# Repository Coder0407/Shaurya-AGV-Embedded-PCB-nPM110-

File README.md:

# Shaurya-AGV-Embedded-PCB-nPM110-

This project involves the design and layout of a high-efficiency Power Management Module based on the Nordic nPM1100 PMIC. The board is engineered to provide a robust 3V logic rail at a nominal 200ma charging rate.
The PCB follows a 2-Layer approach where Copper Pour(Ground) has been done on both planes with a primary focus on maintaining a solid, contiguous Ground Plane on the bottom layer. By minimizing signal routing on the bottom a low-impedance return path for the high-frequency switching currents is ensured 
The Designs prioritises Power integrety , a effort has been made into ensuring minimum SW- trace and keeping the decoupling capacitors as close as possible with multiple ground vias attached to them
Various LED for power CHG and ERR are placed , MCU is exposed to multiple pins including CHG ERR Mode SHPACT and a battery charge monitering system has been introduced.
A switch has also been connected to SHPLD to turn on the IC manually.
Values of various Pins like VSET and resistance like R_ICHG are tune to ensure a 200ma nominal charging current and a max 4.2VBAT with the data from the datasheet.
In the battery monitering system the MCU is given controll through Q1 and Q2 on when to measure the battery voltage, to reduce power loss .

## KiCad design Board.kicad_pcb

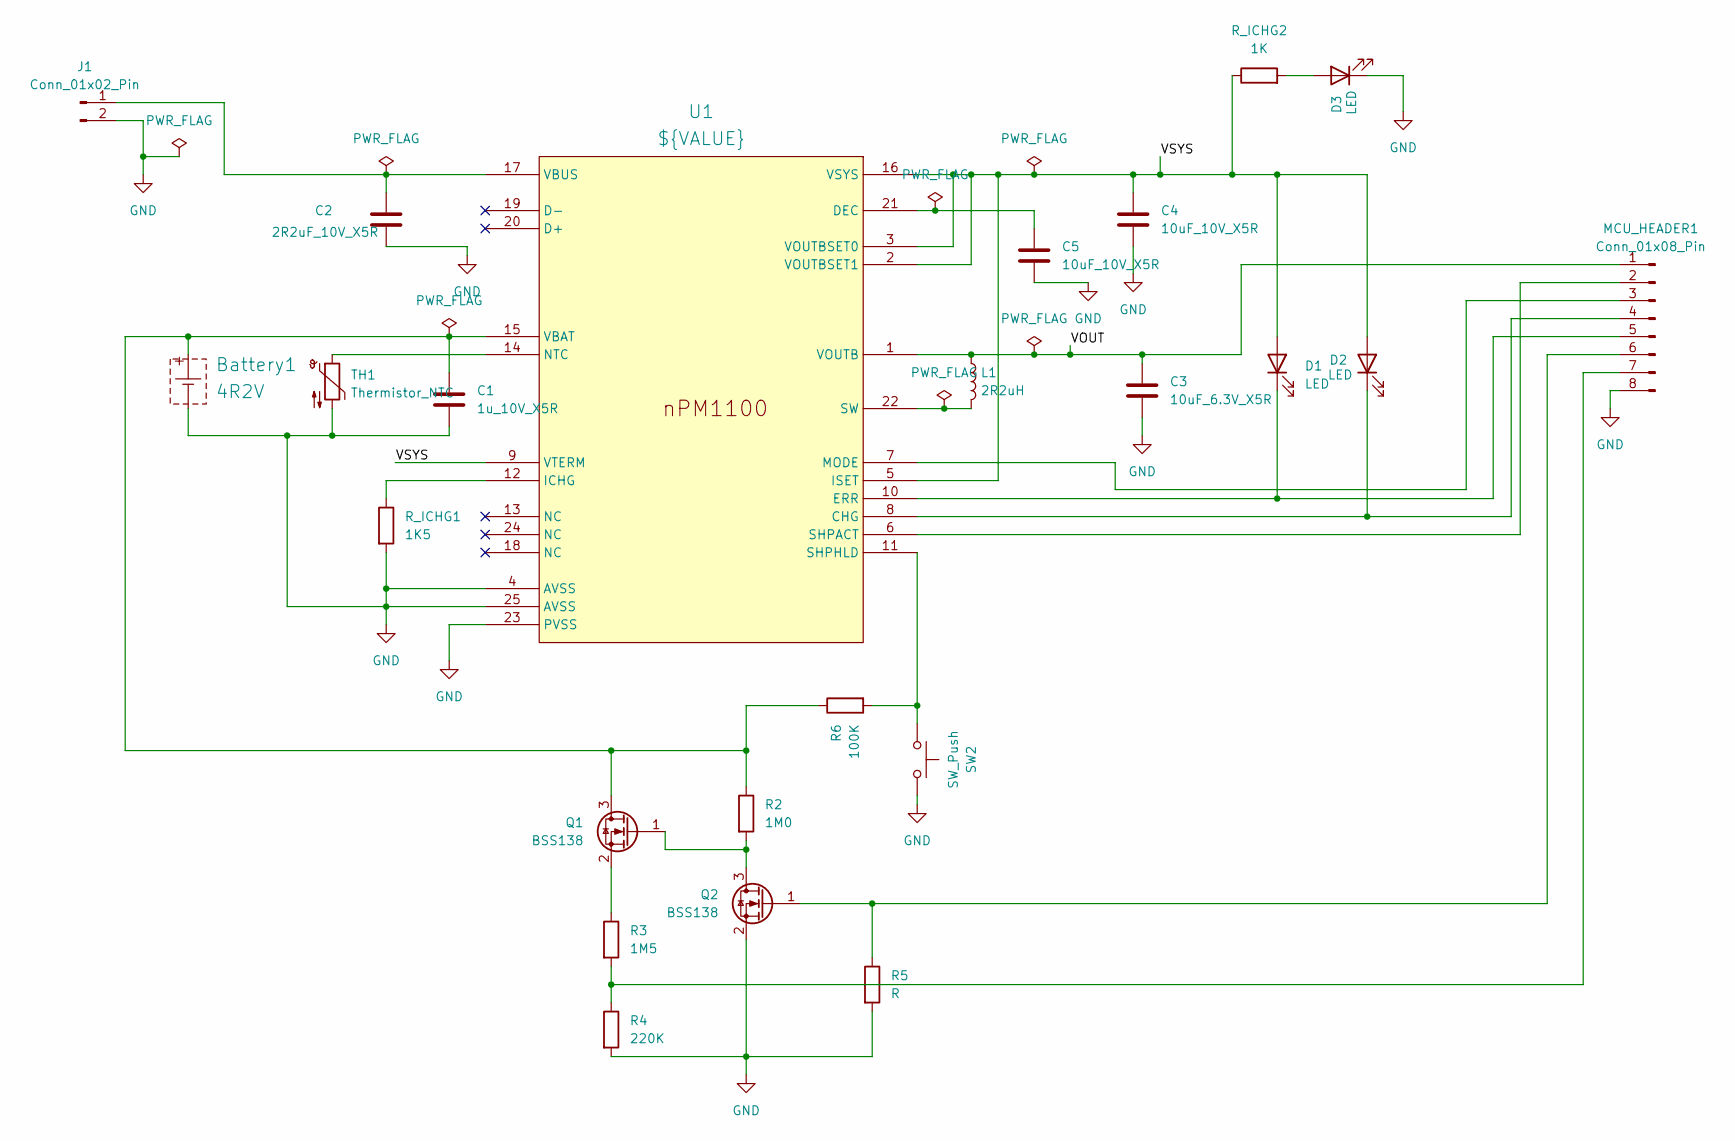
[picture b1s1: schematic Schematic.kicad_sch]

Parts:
Battery1: 4R2V; JST_PH_B2B-PH-SM4-TB_1x02-1MP_P2.00mm_Vertical
C1: 1u_10V_X5R; C_0603_1608Metric_Pad1.08x0.95mm_HandSolder
C2: 2R2uF_10V_X5R; C_0603_1608Metric_Pad1.08x0.95mm_HandSolder
C3: 10uF_6.3V_X5R; C_0603_1608Metric_Pad1.08x0.95mm_HandSolder
C4, C5: 10uF_10V_X5R; C_0603_1608Metric_Pad1.08x0.95mm_HandSolder
D1, D2, D3: LED; LED_0603_1608Metric_Pad1.05x0.95mm_HandSolder
J1: Conn_01x02_Pin; PinHeader_1x02_P2.54mm_Vertical_SMD_Pin1Left
L1: 2R2uH; L_0603_1608Metric_Pad1.05x0.95mm_HandSolder
MCU_HEADER1: Conn_01x08_Pin; PinHeader_1x08_P2.54mm_Vertical_SMD_Pin1Left
Q1, Q2: BSS138; SOT-23
R2: 1M0; R_0603_1608Metric_Pad0.98x0.95mm_HandSolder
R3: 1M5; R_0603_1608Metric_Pad0.98x0.95mm_HandSolder
R4: 220K; R_0603_1608Metric_Pad0.98x0.95mm_HandSolder
R5: R; R_0603_1608Metric_Pad0.98x0.95mm_HandSolder
R6: 100K; R_0603_1608Metric_Pad0.98x0.95mm_HandSolder
R_ICHG1: 1K5; R_0603_1608Metric_Pad0.98x0.95mm_HandSolder
R_ICHG2: 1K; R_0603_1608Metric_Pad0.98x0.95mm_HandSolder
SW2: SW_Push; SW_Push_1P1T_NO_CK_KMR2
TH1: Thermistor_NTC; R_0603_1608Metric_Pad0.98x0.95mm_HandSolder
U1: ${VALUE}; HVQFN-24-1EP_4x4mm_P0.5mm_EP2.6x2.6mm_ThermalVias

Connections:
/VOUT: C3.1, L1.1, MCU_HEADER1.1, U1.1 (VOUTB)
/VSYS: C4.1, D1.2 (A), D2.2 (A), R_ICHG2.1, U1.2 (VOUTBSET1), U1.3 (VOUTBSET0), U1.5 (ISET), U1.9 (VTERM), U1.16 (VSYS)
GND: Battery1.1 (GND), C1.2, C2.2, C3.2, C4.2, C5.2, D3.1 (K), J1.2, MCU_HEADER1.8, Q2.2 (S), R4.2, R5.2, R_ICHG1.2, SW2.1, TH1.2, U1.4 (AVSS), U1.23 (PVSS), U1.25 (AVSS)
unnamed: Battery1.2 (V+), C1.1, Q1.3 (D), R2.1, R6.1, U1.15 (VBAT)
unnamed: D1.1 (K), MCU_HEADER1.5, U1.10 (ERR)
unnamed: D2.1 (K), MCU_HEADER1.4, U1.8 (CHG)
unnamed: D3.2 (A), R_ICHG2.2
unnamed: C2.1, J1.1, U1.17 (VBUS)
unnamed: MCU_HEADER1.2, U1.6 (SHPACT)
unnamed: MCU_HEADER1.3, U1.7 (MODE)
unnamed: MCU_HEADER1.6, Q2.1 (G), R5.1
unnamed: MCU_HEADER1.7, R3.2, R4.1
unnamed: Q1.1 (G), Q2.3 (D), R2.2
unnamed: Q1.2 (S), R3.1
unnamed: C5.1, U1.21 (DEC)
unnamed: R_ICHG1.1, U1.12 (ICHG)
unnamed: TH1.1, U1.14 (NTC)
unnamed: R6.2, SW2.2, U1.11 (SHPHLD)
unnamed: L1.2, U1.22 (SW)

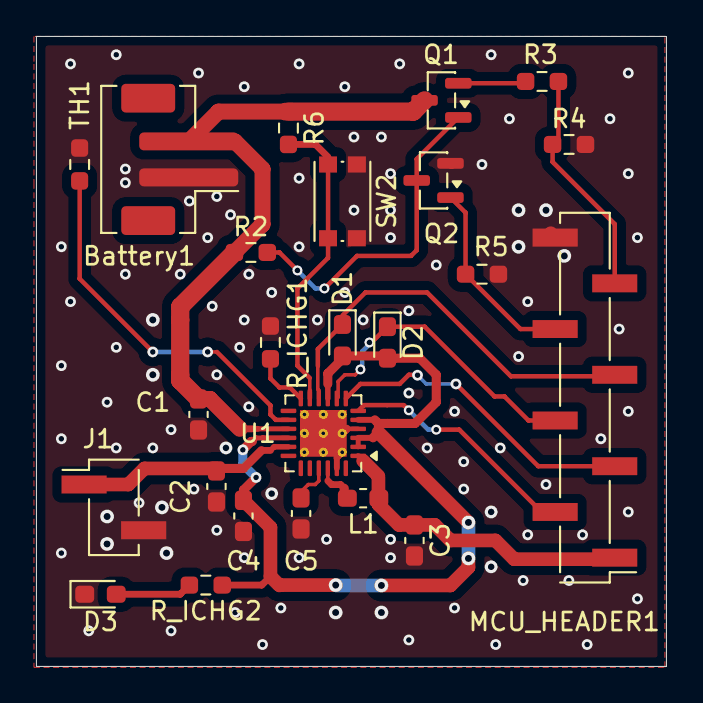
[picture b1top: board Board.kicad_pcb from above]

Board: 2 copper layers, 35.0 x 35.0 mm, 24 parts (0 on the bottom side), 19 nets.

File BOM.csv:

,Qty,Value,DNP,Exclude from BOM,Exclude from Board,Footprint,Datasheet,Manufacturer,,Manufacturer part number,Supplier,Supplier Part number,,
Battery1,1,4R2V,,,,Connector_JST:JST_PH_B2B-PH-SM4-TB_1x02-1MP_P2.00mm_Vertical,,JST,,B2B-PH-SM4-TB(LF)(SN),LSCS,C160352,,
C1,1,1u_10V_X5R,,,,Capacitor_SMD:C_0603_1608Metric_Pad1.08x0.95mm_HandSolder,~,YAGEO,,CC0603KRX5R6BB105,Mouser Electronics`,603-CC603KRX5R6BB105,,
C2,1,2R2uF_10V_X5R,,,,Capacitor_SMD:C_0603_1608Metric_Pad1.08x0.95mm_HandSolder,~,Samsung Electro-Mechanics,,CL10A225KP8NNWC,Mouser Electronics`,187-CL10A225KP8NNWC,,`
C3,1,10uF_6.3V_X5R,,,,Capacitor_SMD:C_0603_1608Metric_Pad1.08x0.95mm_HandSolder,~,Samsung Electro-Mechanics,,CL10A106KP8NQSC,Mouser Electronics`,187-CL10A106KP8NQSC,,
"C4,C5",2,10uF_10V_X5R,,,,Capacitor_SMD:C_0603_1608Metric_Pad1.08x0.95mm_HandSolder,~,Samsung Electro-Mechanics,,CL10A106KP8NQSC,Mouser Electronics`,187-CL10A106KP8NQSC,,
"D1,D2,D3",3,LED,,,,LED_SMD:LED_0603_1608Metric_Pad1.05x0.95mm_HandSolder,~,Wurth Elektronik,,150060RS83000,Mouser Electronics`,710-150060RS83000,,
J1,1,Conn_01x02_Pin,,,,Connector_PinHeader_2.54mm:PinHeader_1x02_P2.54mm_Vertical_SMD_Pin1Left,~,"	
Samtec Inc.",,TSM-102-01-L-SV,Digikey,SAM8979-ND,,
L1,1,2R2uH,,,,Inductor_SMD:L_0603_1608Metric_Pad1.05x0.95mm_HandSolder,~,Murata Electronics,,LQW18FT2R2K0HL,Mouser Electronics`,81-LQW18FT2R2K0HL,,
MCU_HEADER1,1,Conn_01x08_Pin,,,,Connector_PinHeader_2.54mm:PinHeader_1x08_P2.54mm_Vertical_SMD_Pin1Left,~,Mill-Max,,419-10-208-30-055000,Mouser Electronics`,575-4191020830055000,,
"Q1,Q2",2,BSS138,,,,Package_TO_SOT_SMD:SOT-23,https://www.onsemi.com/pub/Collateral/BSS138-D.PDF,onsemi,,BSS138,Mouser Electronics`,512-BSS138,,
"R2,R5",1,1M0,,,,Resistor_SMD:R_0603_1608Metric_Pad0.98x0.95mm_HandSolder,~, Vishay,,CRCW06037K15FKEC,Mouser Electronics`,71-CRCW06037K15FKEC,,
R3,1,1M5,,,,Resistor_SMD:R_0603_1608Metric_Pad0.98x0.95mm_HandSolder,~,Vishay / Draloric,,RCS06031M50FKEA,Mouser Electronics`,71-RCS06031M50FKEA,,
R4,1,220K,,,,Resistor_SMD:R_0603_1608Metric_Pad0.98x0.95mm_HandSolder,~,Vishay / Draloric,,RCS0603220KFKEA,Mouser Electronics`,71-RCS0603220KFKEA,,
R6,1,100K,,,,Resistor_SMD:R_0603_1608Metric_Pad0.98x0.95mm_HandSolder,~,Vishay Dale,,CRCW0603100KFKEA,DigiKey,541-100KHDKR-ND,,
R_ICHG1,1,1K5,,,,Resistor_SMD:R_0603_1608Metric_Pad0.98x0.95mm_HandSolder,~,Susumu,,RG1608P-152-B-T5,DigiKey,RG16P1.5KBDKR-ND,,
R_ICHG2,1,1K,,,,Resistor_SMD:R_0603_1608Metric_Pad0.98x0.95mm_HandSolder,~,Stackpole Electronics Inc,,RMCF0603FT1K00,DigiKey,RMCF0603FT1K00DKR-ND,,
SW2,1,SW_Push,,,,Button_Switch_SMD:SW_Push_1P1T_NO_CK_KMR2,~,C&K,,KMR232NG ULC LFS,Mouser Electronics`,611-KMR232NGULCLFS,,
TH1,1,Thermistor_NTC,,,,Resistor_SMD:R_0603_1608Metric_Pad0.98x0.95mm_HandSolder,~,TDK,,NTCSP164KF104FT1H,Mouser Electronics`,810-NTCSP164KF104FT1,,
U1,1,VALUE,,,,Package_DFN_QFN:HVQFN-24-1EP_4x4mm_P0.5mm_EP2.6x2.6mm_ThermalVias,,Nordic Semiconductor ASA,,4823-NPM1100-QDAA-RDKR-ND,DigiKey,4823-NPM1100-QDAA-RDKR-ND,,

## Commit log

2026-03-30 Enhance README with project details and specifications
    Expanded project description to include details about the Power Management Module design, PCB layout, and features.
